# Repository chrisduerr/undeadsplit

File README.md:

# Undead Split Keyboard (v3)

Undead Split v3 is the third revision of my selfmade split mechanical keyboard.

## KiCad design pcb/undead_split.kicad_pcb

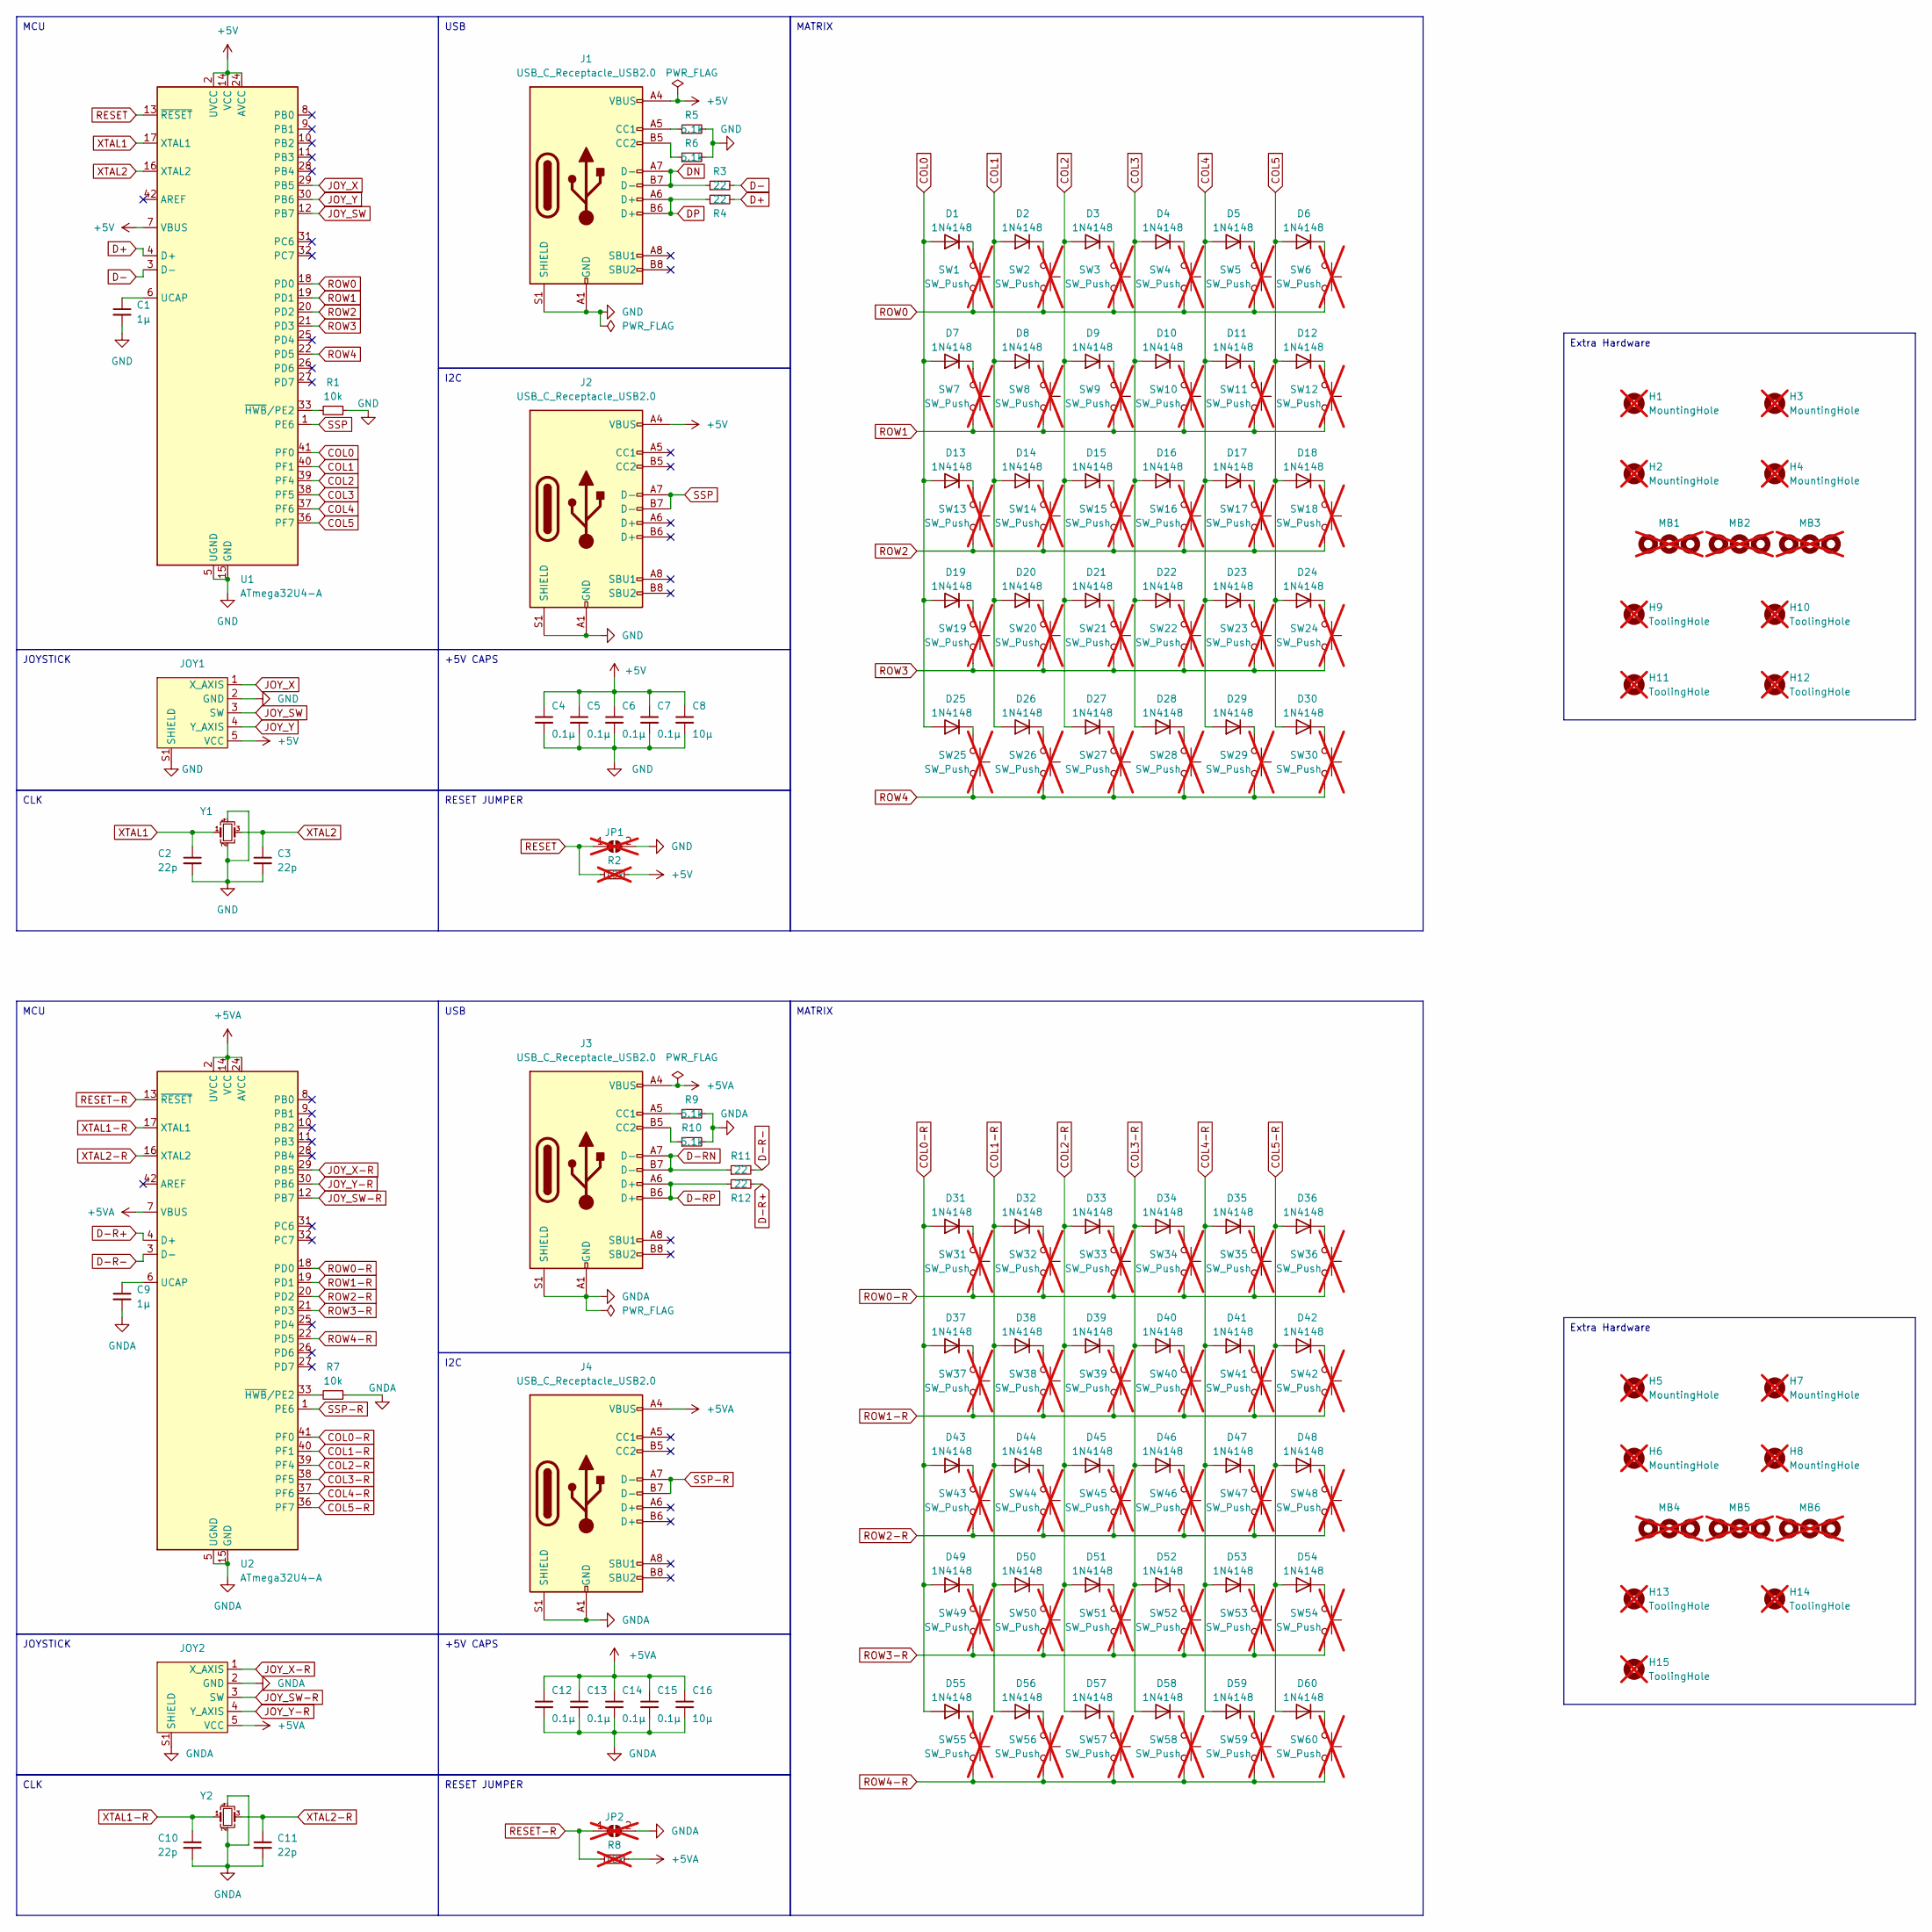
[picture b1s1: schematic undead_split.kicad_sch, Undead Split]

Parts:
C1, C9: 1µ; capacitor; JLCPCB Part # C28323
C2, C3, C10, C11: 22p; capacitor; JLCPCB Part # C1804
C4, C5, C6, C7, C12, C13, C14, C15: 0.1µ; capacitor; JLCPCB Part # C1711
C8, C16: 10µ; capacitor; JLCPCB Part # C17024
D1, D2, D3, D4, D5, D6, D7, D8, D9, D10, D11, D12, D13, D14, D15, D16, D17, D18, D19, D20, D21, D22, D23, D24, D25, D26, D27, D28, D29, D30, D31, D32, D33, D34, D35, D36, D37, D38, D39, D40, D41, D42, D43, D44, D45, D46, D47, D48, D49, D50, D51, D52, D53, D54, D55, D56, D57, D58, D59, D60: 1N4148; D_DO-35_SOD27_P7.62mm_Horizontal; JLCPCB Part # C402212
H1, H2, H3, H4, H5, H6, H7, H8: MountingHole; MountingHole_2.2mm_M2; not fitted
H9, H10, H11, H12, H13, H14, H15: ToolingHole; tooling_hole; not fitted
J1, J2, J3, J4: USB_C_Receptacle_USB2.0; USB_C_Receptacle_GCT_USB4105-xx-A_16P_TopMnt_Horizontal; JLCPCB Part # C393939
JOY1, JOY2: joycon_joystick; JLCPCB Part # C5213747
JP1, JP2: SolderJumper-2_P1.3mm_Open_Pad1.0x1.5mm; not fitted
MB1, MB2, MB3, MB4, MB5, MB6: mouse_bites; not fitted
R1, R7: 10k; resistor; JLCPCB Part # C17414
R2, R8: 10k; resistor; JLCPCB Part # C17414; not fitted
R3, R4, R11, R12: 22; resistor; JLCPCB Part # C17561
R5, R6, R9, R10: 5.1k; resistor; JLCPCB Part # C27834
SW1, SW2, SW3, SW4, SW5, SW6, SW7, SW8, SW9, SW10, SW11, SW12, SW13, SW14, SW15, SW16, SW17, SW18, SW19, SW20, SW21, SW22, SW23, SW24, SW25, SW26, SW27, SW28, SW29, SW30, SW31, SW32, SW33, SW34, SW35, SW36, SW37, SW38, SW39, SW40, SW41, SW42, SW43, SW44, SW45, SW46, SW47, SW48, SW49, SW50, SW51, SW52, SW53, SW54, SW55, SW56, SW57, SW58, SW59, SW60: SW_Push; CherryMX_Hotswap; not fitted
U1, U2: ATmega32U4-A; TQFP-44_10x10mm_P0.8mm; JLCPCB Part # C44854
Y1, Y2: Crystal_SMD_3225-4Pin_3.2x2.5mm_HandSoldering; JLCPCB Part # C13738

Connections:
+5V: C4.1, C5.1, C6.1, C7.1, C8.1, J1.A4 (VBUS), J1.A9 (VBUS), J1.B4 (VBUS), J1.B9 (VBUS), J2.A4 (VBUS), J2.A9 (VBUS), J2.B4 (VBUS), J2.B9 (VBUS), JOY1.5 (VCC), R2.2, U1.2 (UVCC), U1.7 (VBUS), U1.14 (VCC), U1.24 (AVCC), U1.34 (VCC), U1.44 (AVCC)
+5VA: C12.1, C13.1, C14.1, C15.1, C16.1, J3.A4 (VBUS), J3.A9 (VBUS), J3.B4 (VBUS), J3.B9 (VBUS), J4.A4 (VBUS), J4.A9 (VBUS), J4.B4 (VBUS), J4.B9 (VBUS), JOY2.5 (VCC), R8.2, U2.2 (UVCC), U2.7 (VBUS), U2.14 (VCC), U2.24 (AVCC), U2.34 (VCC), U2.44 (AVCC)
COL0: D1.2 (A), D7.2 (A), D13.2 (A), D19.2 (A), D25.2 (A), U1.41 (PF0)
COL0-R: D31.2 (A), D37.2 (A), D43.2 (A), D49.2 (A), D55.2 (A), U2.41 (PF0)
COL1: D2.2 (A), D8.2 (A), D14.2 (A), D20.2 (A), D26.2 (A), U1.40 (PF1)
COL1-R: D32.2 (A), D38.2 (A), D44.2 (A), D50.2 (A), D56.2 (A), U2.40 (PF1)
COL2: D3.2 (A), D9.2 (A), D15.2 (A), D21.2 (A), D27.2 (A), U1.39 (PF4)
COL2-R: D33.2 (A), D39.2 (A), D45.2 (A), D51.2 (A), D57.2 (A), U2.39 (PF4)
COL3: D4.2 (A), D10.2 (A), D16.2 (A), D22.2 (A), D28.2 (A), U1.38 (PF5)
COL3-R: D34.2 (A), D40.2 (A), D46.2 (A), D52.2 (A), D58.2 (A), U2.38 (PF5)
COL4: D5.2 (A), D11.2 (A), D17.2 (A), D23.2 (A), D29.2 (A), U1.37 (PF6)
COL4-R: D35.2 (A), D41.2 (A), D47.2 (A), D53.2 (A), D59.2 (A), U2.37 (PF6)
COL5: D6.2 (A), D12.2 (A), D18.2 (A), D24.2 (A), D30.2 (A), U1.36 (PF7)
COL5-R: D36.2 (A), D42.2 (A), D48.2 (A), D54.2 (A), D60.2 (A), U2.36 (PF7)
D+: R4.2, U1.4 (D+)
D-: R3.2, U1.3 (D-)
D-R+: R12.2, U2.4 (D+)
D-R-: R11.2, U2.3 (D-)
D-RN: J3.A7 (D-), J3.B7 (D-), R11.1
D-RP: J3.A6 (D+), J3.B6 (D+), R12.1
DN: J1.A7 (D-), J1.B7 (D-), R3.1
DP: J1.A6 (D+), J1.B6 (D+), R4.1
GND: C1.2, C2.2, C3.2, C4.2, C5.2, C6.2, C7.2, C8.2, J1.A1 (GND), J1.A12 (GND), J1.B1 (GND), J1.B12 (GND), J1.S1 (SHIELD), J2.A1 (GND), J2.A12 (GND), J2.B1 (GND), J2.B12 (GND), J2.S1 (SHIELD), JOY1.2 (GND), JOY1.S1 (SHIELD), JP1.2 (B), R1.1, R5.2, R6.2, U1.5 (UGND), U1.15 (GND), U1.23 (GND), U1.35 (GND), U1.43 (GND), Y1.2, Y1.4
GNDA: C9.2, C10.2, C11.2, C12.2, C13.2, C14.2, C15.2, C16.2, J3.A1 (GND), J3.A12 (GND), J3.B1 (GND), J3.B12 (GND), J3.S1 (SHIELD), J4.A1 (GND), J4.A12 (GND), J4.B1 (GND), J4.B12 (GND), J4.S1 (SHIELD), JOY2.2 (GND), JOY2.S1 (SHIELD), JP2.2 (B), R7.1, R9.2, R10.2, U2.5 (UGND), U2.15 (GND), U2.23 (GND), U2.35 (GND), U2.43 (GND), Y2.2, Y2.4
JOY_SW: JOY1.3 (SW), U1.12 (PB7)
JOY_SW-R: JOY2.3 (SW), U2.12 (PB7)
JOY_X: JOY1.1 (X_AXIS), U1.29 (PB5)
JOY_X-R: JOY2.1 (X_AXIS), U2.29 (PB5)
JOY_Y: JOY1.4 (Y_AXIS), U1.30 (PB6)
JOY_Y-R: JOY2.4 (Y_AXIS), U2.30 (PB6)
unnamed: D1.1 (K), SW1.1
unnamed: D2.1 (K), SW2.1
unnamed: D3.1 (K), SW3.1
unnamed: D4.1 (K), SW4.1
unnamed: D5.1 (K), SW5.1
unnamed: D6.1 (K), SW6.1
unnamed: D7.1 (K), SW7.1
unnamed: D8.1 (K), SW8.1
unnamed: D9.1 (K), SW9.1
unnamed: D10.1 (K), SW10.1
unnamed: D11.1 (K), SW11.1
unnamed: D12.1 (K), SW12.1
unnamed: D13.1 (K), SW13.1
unnamed: D14.1 (K), SW14.1
unnamed: D15.1 (K), SW15.1
unnamed: D16.1 (K), SW16.1
unnamed: D17.1 (K), SW17.1
unnamed: D18.1 (K), SW18.1
unnamed: D19.1 (K), SW19.1
unnamed: D20.1 (K), SW20.1
unnamed: D21.1 (K), SW21.1
unnamed: D22.1 (K), SW22.1
unnamed: D23.1 (K), SW23.1
unnamed: D24.1 (K), SW24.1
unnamed: D25.1 (K), SW25.1
unnamed: D26.1 (K), SW26.1
unnamed: D27.1 (K), SW27.1
unnamed: D28.1 (K), SW28.1
unnamed: D29.1 (K), SW29.1
unnamed: D30.1 (K), SW30.1
unnamed: D31.1 (K), SW31.1
unnamed: D32.1 (K), SW32.1
unnamed: D33.1 (K), SW33.1
unnamed: D34.1 (K), SW34.1
unnamed: D35.1 (K), SW35.1
unnamed: D36.1 (K), SW36.1
unnamed: D37.1 (K), SW37.1
unnamed: D38.1 (K), SW38.1
unnamed: D39.1 (K), SW39.1
unnamed: D40.1 (K), SW40.1
unnamed: D41.1 (K), SW41.1
unnamed: D42.1 (K), SW42.1
unnamed: D43.1 (K), SW43.1
unnamed: D44.1 (K), SW44.1
unnamed: D45.1 (K), SW45.1
unnamed: D46.1 (K), SW46.1
unnamed: D47.1 (K), SW47.1
unnamed: D48.1 (K), SW48.1
unnamed: D49.1 (K), SW49.1
unnamed: D50.1 (K), SW50.1
unnamed: D51.1 (K), SW51.1
unnamed: D52.1 (K), SW52.1
unnamed: D53.1 (K), SW53.1
unnamed: D54.1 (K), SW54.1
unnamed: D55.1 (K), SW55.1
unnamed: D56.1 (K), SW56.1
unnamed: D57.1 (K), SW57.1
unnamed: D58.1 (K), SW58.1
unnamed: D59.1 (K), SW59.1
unnamed: D60.1 (K), SW60.1
unnamed: J1.A5 (CC1), R5.1
unnamed: J1.B5 (CC2), R6.1
unnamed: J3.A5 (CC1), R9.1
unnamed: J3.B5 (CC2), R10.1
unnamed: C1.1, U1.6 (UCAP)
unnamed: R1.2, U1.33 (~HWB/PE2)
unnamed: C9.1, U2.6 (UCAP)
unnamed: R7.2, U2.33 (~HWB/PE2)
RESET: JP1.1 (A), R2.1, U1.13 (~RESET)
RESET-R: JP2.1 (A), R8.1, U2.13 (~RESET)
ROW0: SW1.2, SW2.2, SW3.2, SW4.2, SW5.2, SW6.2, U1.18 (PD0)
ROW0-R: SW31.2, SW32.2, SW33.2, SW34.2, SW35.2, SW36.2, U2.18 (PD0)
ROW1: SW7.2, SW8.2, SW9.2, SW10.2, SW11.2, SW12.2, U1.19 (PD1)
ROW1-R: SW37.2, SW38.2, SW39.2, SW40.2, SW41.2, SW42.2, U2.19 (PD1)
ROW2: SW13.2, SW14.2, SW15.2, SW16.2, SW17.2, SW18.2, U1.20 (PD2)
ROW2-R: SW43.2, SW44.2, SW45.2, SW46.2, SW47.2, SW48.2, U2.20 (PD2)
ROW3: SW19.2, SW20.2, SW21.2, SW22.2, SW23.2, SW24.2, U1.21 (PD3)
ROW3-R: SW49.2, SW50.2, SW51.2, SW52.2, SW53.2, SW54.2, U2.21 (PD3)
ROW4: SW25.2, SW26.2, SW27.2, SW28.2, SW29.2, SW30.2, U1.22 (PD5)
ROW4-R: SW55.2, SW56.2, SW57.2, SW58.2, SW59.2, SW60.2, U2.22 (PD5)
SSP: J2.A7 (D-), J2.B7 (D-), U1.1 (PE6)
SSP-R: J4.A7 (D-), J4.B7 (D-), U2.1 (PE6)
XTAL1: C2.1, U1.17 (XTAL1), Y1.1
XTAL1-R: C10.1, U2.17 (XTAL1), Y2.1
XTAL2: C3.1, U1.16 (XTAL2), Y1.3
XTAL2-R: C11.1, U2.16 (XTAL2), Y2.3

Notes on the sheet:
CLK
Extra Hardware
JOYSTICK
MCU
MATRIX
+5V CAPS
RESET JUMPER
I2C
USB

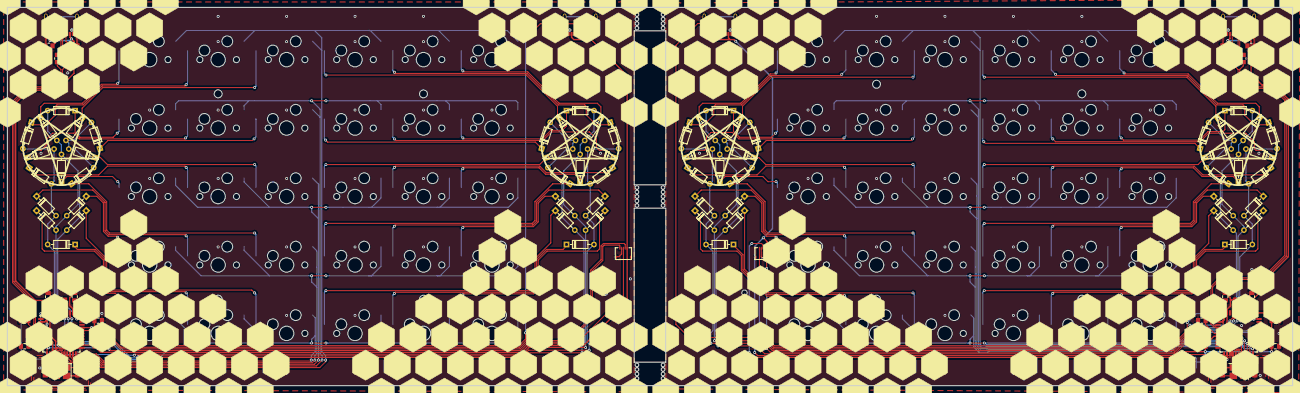
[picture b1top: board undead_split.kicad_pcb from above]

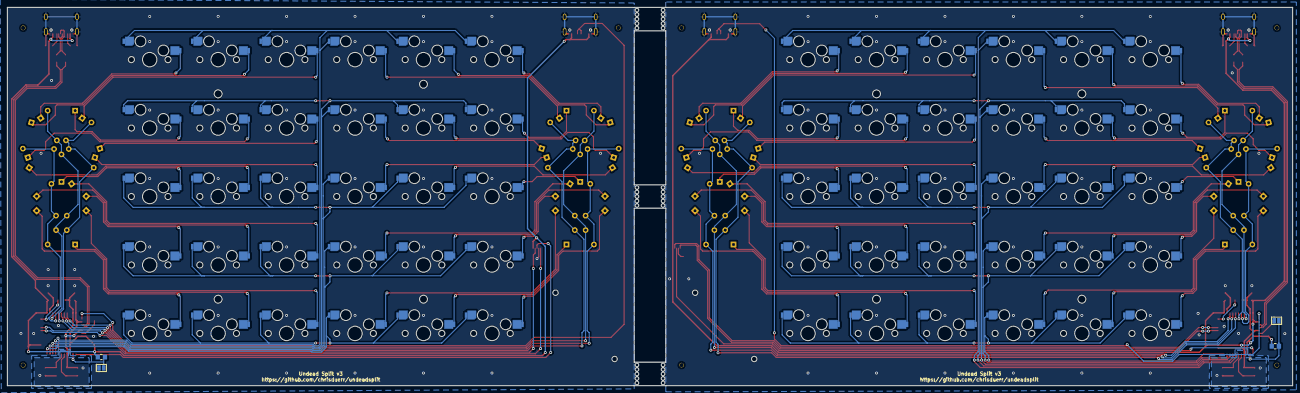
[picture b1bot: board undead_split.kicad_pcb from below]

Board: 2 copper layers, 356.8 x 105.0 mm, 181 parts (4 on the bottom side), 116 nets.

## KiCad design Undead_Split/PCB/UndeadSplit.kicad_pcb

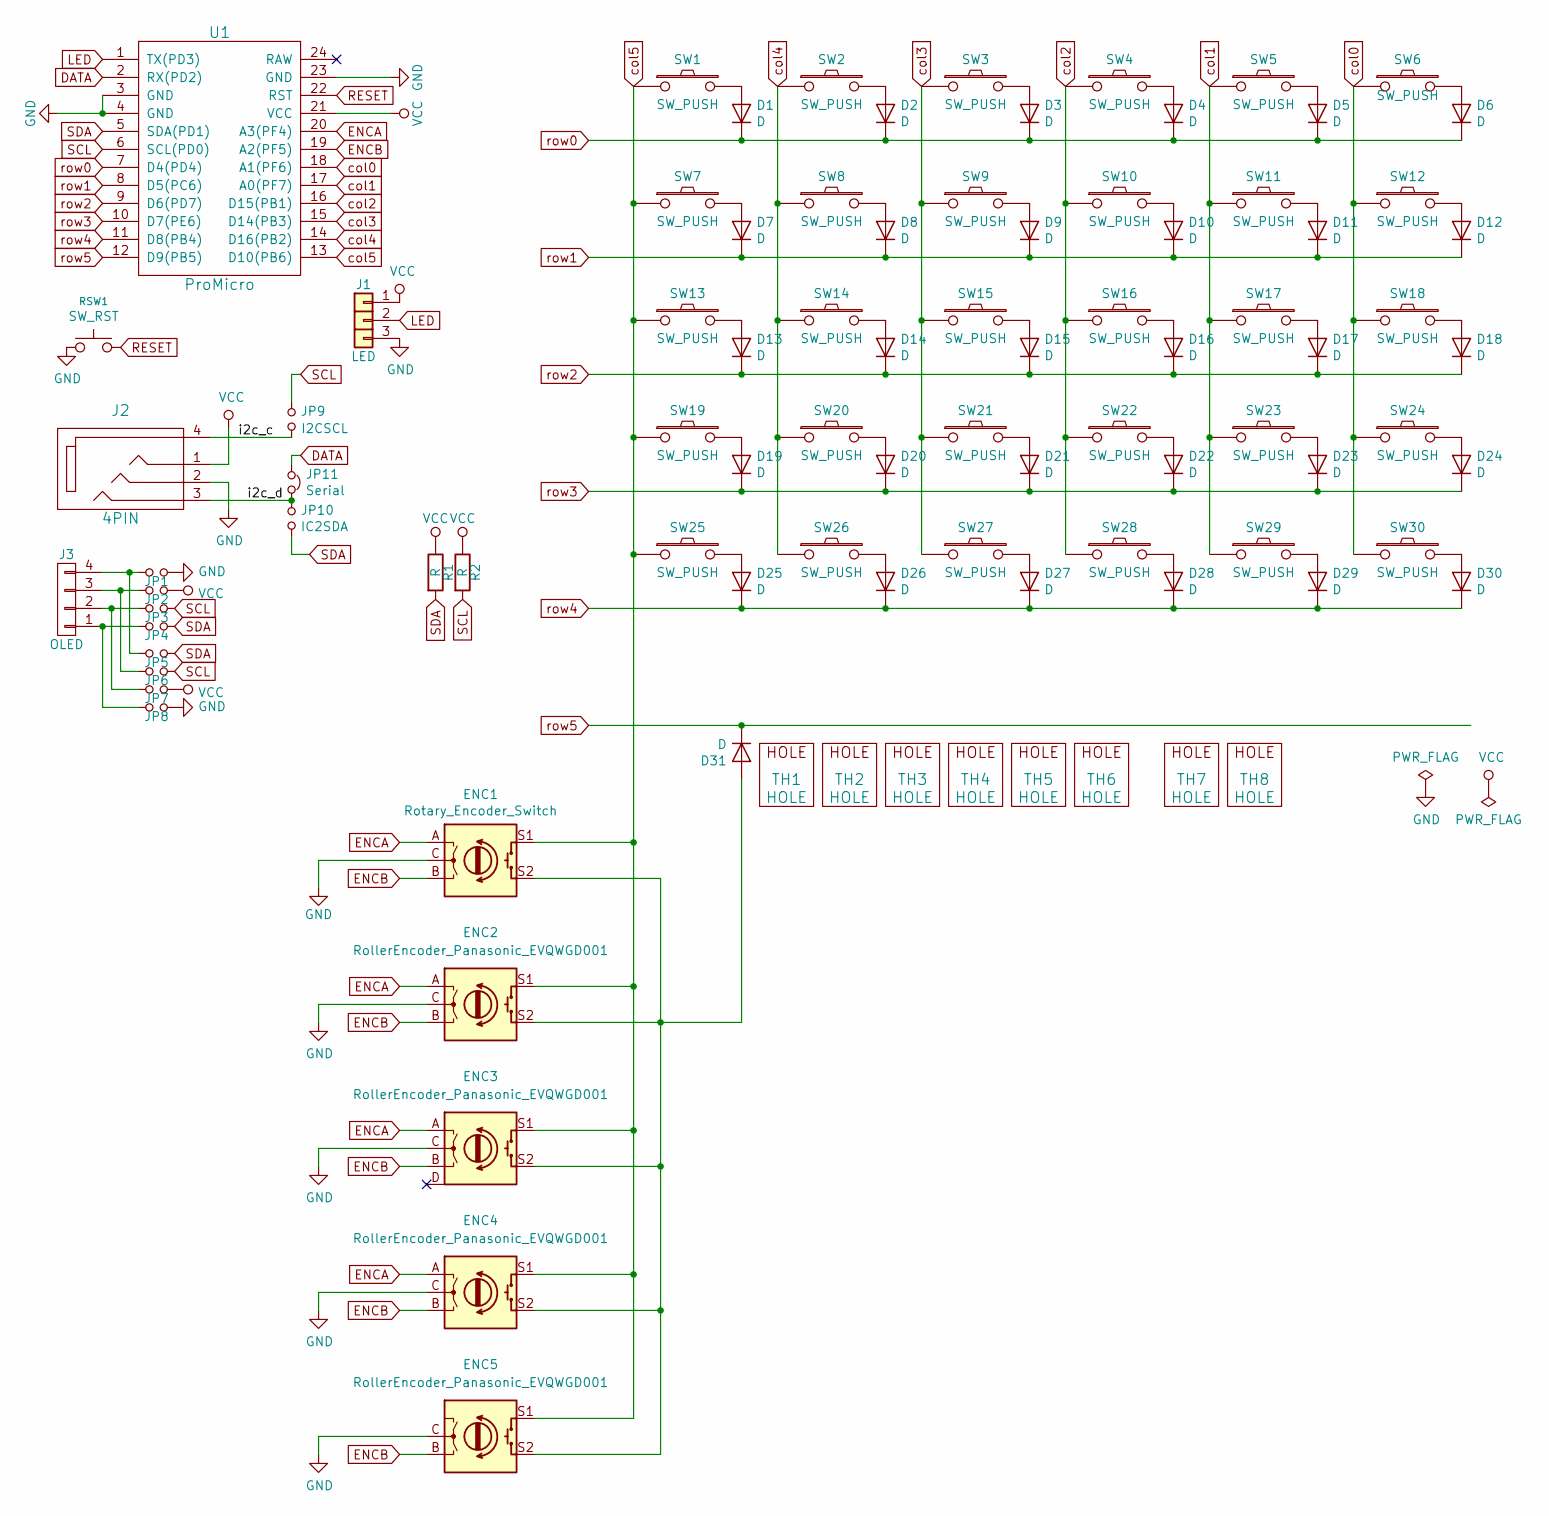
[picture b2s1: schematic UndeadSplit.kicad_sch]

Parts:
D1, D2, D3, D4, D5, D6, D7, D8, D9, D10, D11, D12, D13, D14, D15, D16, D17, D18, D19, D20, D21, D22, D23, D24, D25, D26, D27, D28, D29, D30, D31: D; Diode_SOD123
ENC1: Rotary_Encoder_Switch; RotaryEncoder_Alps_EC11E-Switch_Vertical_H20mm-keebio_modif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
ENC2, ENC3, ENC4, ENC5: RollerEncoder_Panasonic_EVQWGD001
J1: LED
J2: 4PIN; MJ-4PP-9
J3: OLED; OLED_4Pin
JP1, JP2, JP3, JP4, JP5, JP6, JP7, JP8: Jumper_NO_Small; Jumper
JP9: I2CSCL; SolderJumper-2_P1.3mm_Open_TrianglePad1.0x1.5mm
JP10: IC2SDA; SolderJumper-2_P1.3mm_Open_TrianglePad1.0x1.5mm
JP11: Serial; SolderJumper-2_P1.3mm_Bridged2Bar_Pad1.0x1.5mm
R1, R2: R; R_1206_DoubleSided
RSW1: SW_RST; TACT_SWITCH_TVBP06
SW1, SW2, SW3, SW4, SW5, SW6, SW7, SW8, SW9, SW10, SW11, SW12, SW13, SW14, SW15, SW16, SW17, SW18, SW19, SW20, SW21, SW22, SW23, SW24, SW25, SW26, SW27, SW28, SW29, SW30: SW_PUSH; CherryMX_Hotswap
TH1, TH2, TH3, TH4, TH5, TH6: HOLE; HOLE_M2_TH
TH7, TH8: HOLE; M2_HOLE_PCB
U1: ProMicro; ArduinoProMicro-ZigZag-DoubleSided

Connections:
/i2c_c: J2.4, JP9.2
/i2c_d: J2.3, JP10.1, JP11.2
DATA: JP11.1, U1.2 (RX(PD2))
ENCA: ENC1.A, ENC2.A, ENC3.A, ENC4.A, U1.20 (A3(PF4))
ENCB: ENC1.B, ENC2.B, ENC3.B, ENC4.B, ENC5.B, U1.19 (A2(PF5))
GND: ENC1.C, ENC2.C, ENC3.C, ENC4.C, ENC5.C, J1.3, J2.2, JP1.2, JP8.2, RSW1.1, U1.3 (GND), U1.4 (GND), U1.23 (GND)
LED: J1.2, U1.1 (TX(PD3))
unnamed: D1.2 (A), SW1.2
unnamed: D2.2 (A), SW2.2
unnamed: D3.2 (A), SW3.2
unnamed: D4.2 (A), SW4.2
unnamed: D5.2 (A), SW5.2
unnamed: D6.2 (A), SW6.2
unnamed: D7.2 (A), SW7.2
unnamed: D8.2 (A), SW8.2
unnamed: D9.2 (A), SW9.2
unnamed: D10.2 (A), SW10.2
unnamed: D11.2 (A), SW11.2
unnamed: D12.2 (A), SW12.2
unnamed: D13.2 (A), SW13.2
unnamed: D14.2 (A), SW14.2
unnamed: D15.2 (A), SW15.2
unnamed: D16.2 (A), SW16.2
unnamed: D17.2 (A), SW17.2
unnamed: D18.2 (A), SW18.2
unnamed: D19.2 (A), SW19.2
unnamed: D20.2 (A), SW20.2
unnamed: D21.2 (A), SW21.2
unnamed: D22.2 (A), SW22.2
unnamed: D23.2 (A), SW23.2
unnamed: D24.2 (A), SW24.2
unnamed: D25.2 (A), SW25.2
unnamed: D26.2 (A), SW26.2
unnamed: D27.2 (A), SW27.2
unnamed: D28.2 (A), SW28.2
unnamed: D29.2 (A), SW29.2
unnamed: D30.2 (A), SW30.2
unnamed: D31.2 (A), ENC1.S2, ENC2.S2, ENC3.S2, ENC4.S2, ENC5.S2
unnamed: J3.1, JP4.1, JP8.1
unnamed: J3.2, JP3.1, JP7.1
unnamed: J3.3, JP2.1, JP6.1
unnamed: J3.4, JP1.1, JP5.1
RESET: RSW1.2, U1.22 (RST)
SCL: JP3.2, JP6.2, JP9.1, R2.2, U1.6 (SCL(PD0))
SDA: JP4.2, JP5.2, JP10.2, R1.2, U1.5 (SDA(PD1))
VCC: J1.1, J2.1, JP2.2, JP7.2, R1.1, R2.1, U1.21 (VCC)
col0: SW6.1, SW12.1, SW18.1, SW24.1, SW30.1, U1.18 (A1(PF6))
col1: SW5.1, SW11.1, SW17.1, SW23.1, SW29.1, U1.17 (A0(PF7))
col2: SW4.1, SW10.1, SW16.1, SW22.1, SW28.1, U1.16 (D15(PB1))
col3: SW3.1, SW9.1, SW15.1, SW21.1, SW27.1, U1.15 (D14(PB3))
col4: SW2.1, SW8.1, SW14.1, SW20.1, SW26.1, U1.14 (D16(PB2))
col5: ENC1.S1, ENC2.S1, ENC3.S1, ENC4.S1, ENC5.S1, SW1.1, SW7.1, SW13.1, SW19.1, SW25.1, U1.13 (D10(PB6))
row0: D1.1 (K), D2.1 (K), D3.1 (K), D4.1 (K), D5.1 (K), D6.1 (K), U1.7 (D4(PD4))
row1: D7.1 (K), D8.1 (K), D9.1 (K), D10.1 (K), D11.1 (K), D12.1 (K), U1.8 (D5(PC6))
row2: D13.1 (K), D14.1 (K), D15.1 (K), D16.1 (K), D17.1 (K), D18.1 (K), U1.9 (D6(PD7))
row3: D19.1 (K), D20.1 (K), D21.1 (K), D22.1 (K), D23.1 (K), D24.1 (K), U1.10 (D7(PE6))
row4: D25.1 (K), D26.1 (K), D27.1 (K), D28.1 (K), D29.1 (K), D30.1 (K), U1.11 (D8(PB4))
row5: D31.1 (K), U1.12 (D9(PB5))

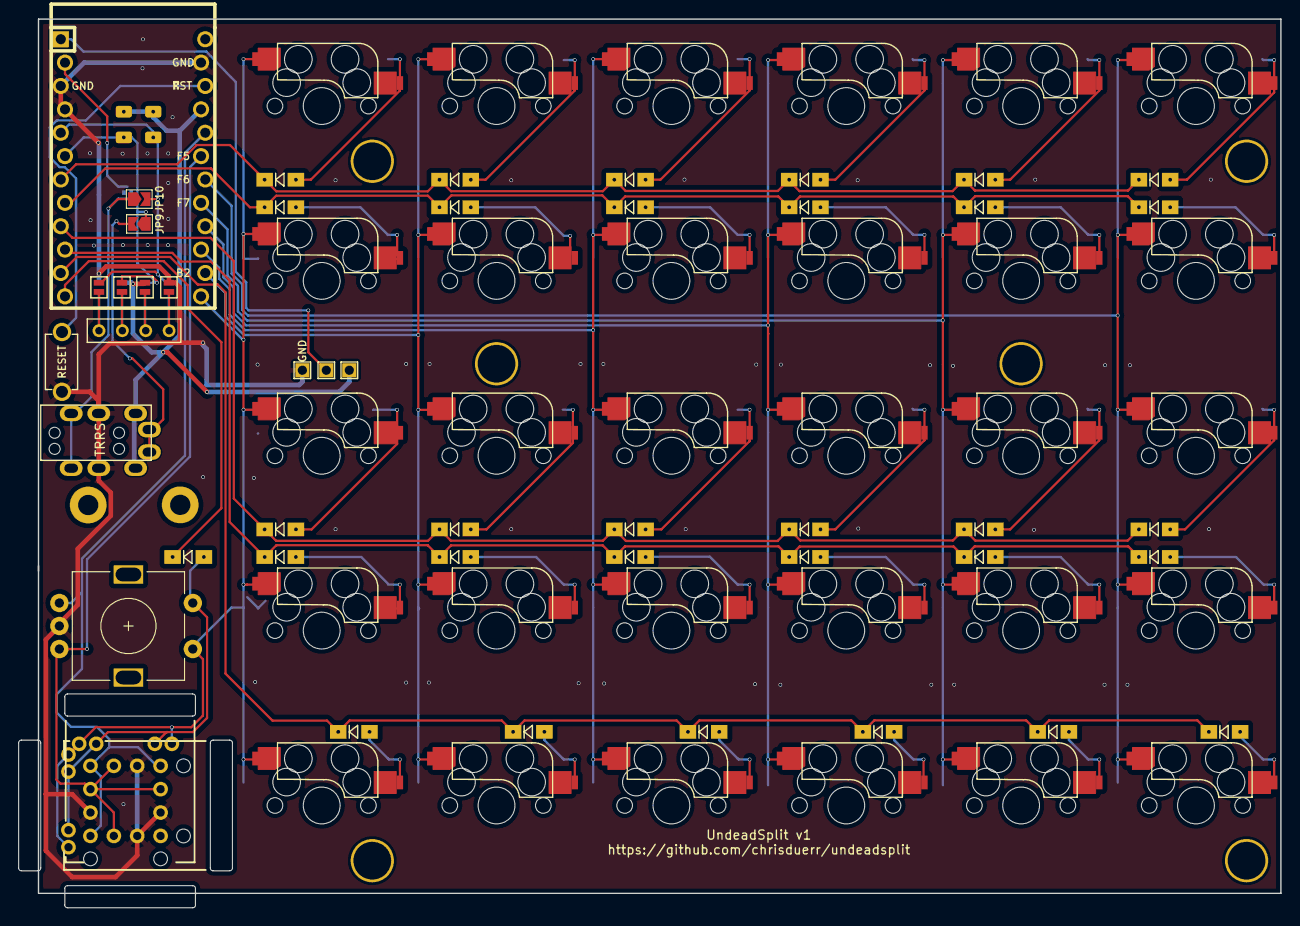
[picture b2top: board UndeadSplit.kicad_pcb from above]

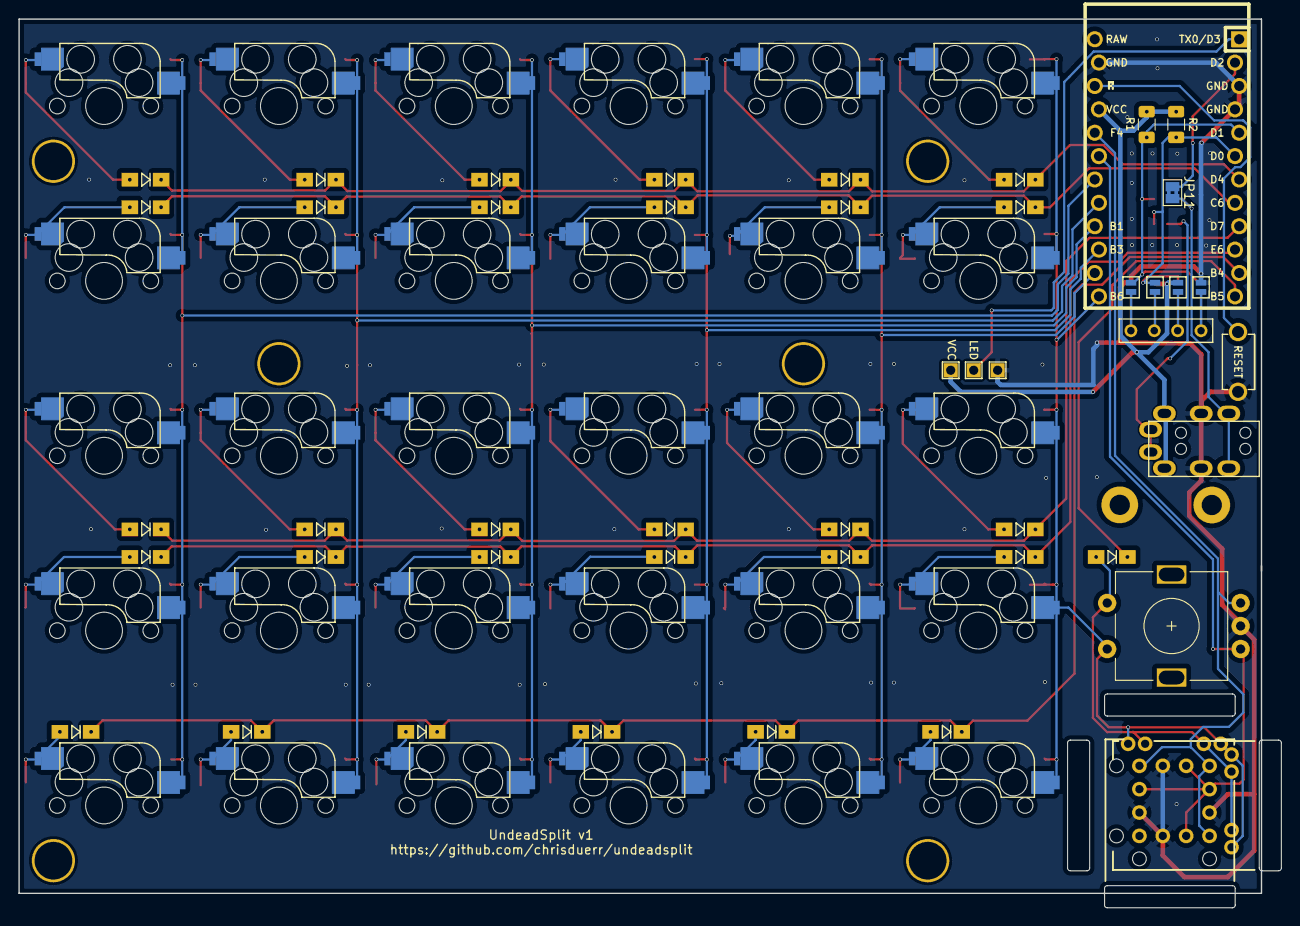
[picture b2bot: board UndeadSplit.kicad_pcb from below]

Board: 2 copper layers, 137.1 x 96.5 mm, 92 parts (9 on the bottom side), 58 nets.

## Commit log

2022-10-10 Add UndeadSplit PCB
2022-10-23 Add pictures
2023-09-06 Add keyboard case
2023-10-12 Add version 2
2023-10-12 Update git config files
2023-10-12 WIP: Case
2023-10-15 Add readme
2024-12-27 Add final v2 case
    This adds the case as used in version 2 of the keyboard. There are some
    clearance issues with the sticks but it does work after some manual
    intervention which is not visible once assembled.
2024-12-27 Remove backup files
    These files are unnecessary since the project is tracked in git anyway.
2024-12-28 Fix joycon alignment
    This fixes an issue with the joycon where it was incorrectly centered to
    the chassis, instead of being centered to the joycon. This has caused a
    slight misalignment of the joycon since it is not centered in its case.
2024-12-29 Add JLCPCB part IDs
2024-12-29 Add JLCPCB production requirements
2024-12-29 Fix footprint position and rotation
    This change allows for easy JLCPCB production without having to perform
    any manual placement or rotation steps.
2024-12-29 Add .gitignore
2025-01-07 Fix version on silkscreen
2025-01-07 Remove hole labels from silkscreen
2025-01-07 Fix vertical joycon alignment
2025-01-07 Update readme for v3
2025-04-27 Update to new KiCad version
2025-04-27 Remove additional labels from PCB
